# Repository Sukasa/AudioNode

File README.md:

# AudioNode
ESP8266/Teensy/VS1063a-based streaming audio node with MQTT integration

This project is the motherboard for a multi-mcu audio endpoint.  It uses three CPUs; a VS1063a does the heavy lifting for the audio decoding and is operated as a slave co-processor by the ESP8266.  A Teensy 3.2 also hangs off the ESP8266, being used as a sub-processor for the touch interface (7 capacitive touch points).  The ESP controls these two processors through a shared SPI bus, with the ESP as the bus master and the Teensy/VS1063a as SPI slaves.

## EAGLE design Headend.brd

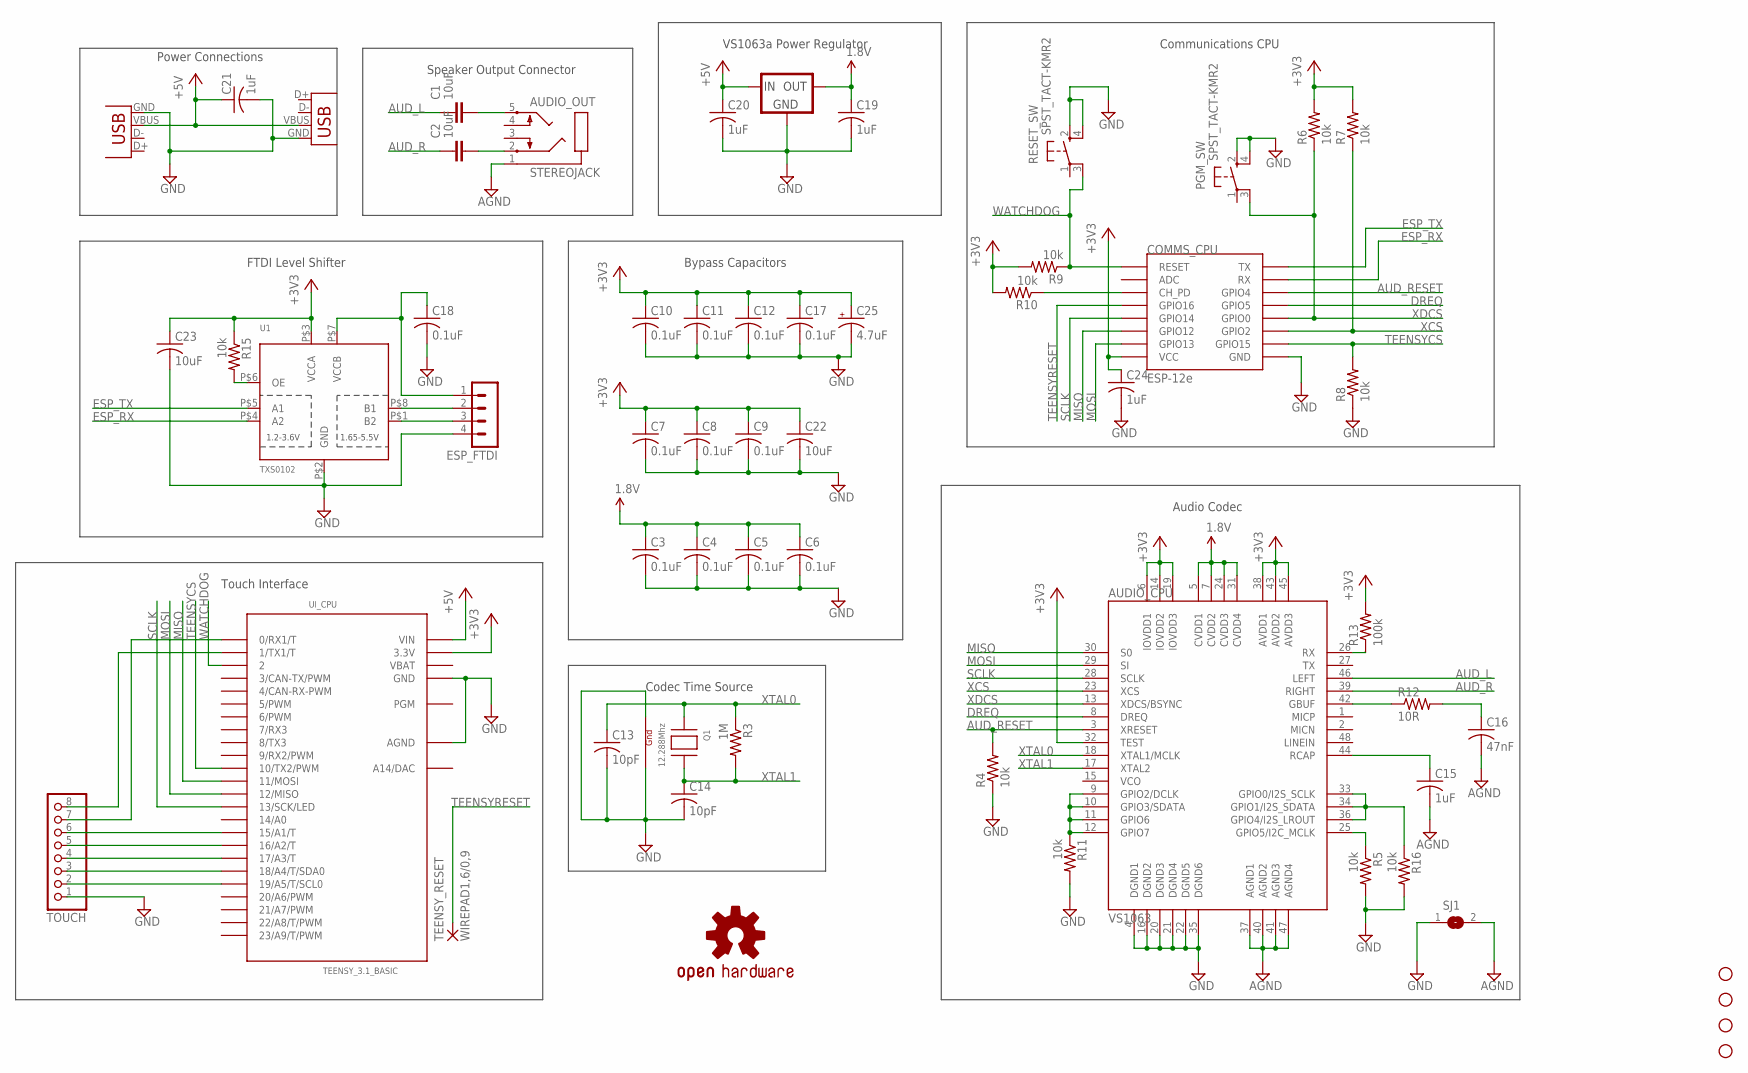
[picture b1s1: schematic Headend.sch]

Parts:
AUDIO_CPU: VS1063; LQFP-48
AUDIO_OUT: STEREOJACK; STX3100
C1, C2: 10uF; C805
C3, C4, C5, C6, C7, C8, C9, C10, C11, C12, C17, C18: 0.1uF; C0402
C13, C14: 10pF; C0402
C15, C24: 1uF; C0402
C16: 47nF; C0402
C19, C20, C21: 1uF; C0603
C22, C23: 10uF; C0402
C25: 4.7uF; PANASONIC_A
COMMS_CPU: ESP-12e; ESP12-SMD
ESP_FTDI: MA04-1
LOGO1: OSHW-LOGOL; OSHW-LOGO-L
PGM_SW: SPST_TACT-KMR2; KMR2
POWER_IN: USBSMD; USB-MINIB
Q1: 12.288Mhz; NX3225
R3: 1M; R0402
R4, R5, R6, R7, R8, R10, R11, R15, R16: 10k; R0402
R9: 10k; R0603
R12: 10R; R0402
R13: 100k; R0402
RESET_SW: SPST_TACT-KMR2; KMR2
SJ1: SJ
SPEAKER_PWR2: USB-A-S
STANDOFF1, STANDOFF2, STANDOFF3, STANDOFF4: STAND-OFF
TEENSY_RESET: WIREPAD1,6/0,9; 1,6/0,9
TOUCH: PINHD-1X8BIG; 1X08-BIG
U1: TXS0102; VFSOP-8
U2: AP7313; SOT23
UI_CPU: TEENSY_3.1_BASIC

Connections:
1.8V: AUDIO_CPU.5 (CVDD1), AUDIO_CPU.7 (CVDD2), AUDIO_CPU.24 (CVDD3), AUDIO_CPU.31 (CVDD4), C3.1, C4.1, C5.1, C6.1, C19.1, U2.2 (OUT)
+3V3: AUDIO_CPU.6 (IOVDD1), AUDIO_CPU.14 (IOVDD2), AUDIO_CPU.19 (IOVDD3), AUDIO_CPU.32 (TEST), AUDIO_CPU.38 (AVDD1), AUDIO_CPU.43 (AVDD2), AUDIO_CPU.45 (AVDD3), C7.1, C8.1, C9.1, C10.1, C11.1, C12.1, C17.1, C22.1, C23.1, C24.1, C25.+, COMMS_CPU.VCC, R6.2, R7.2, R9.2, R10.2, R13.2, R15.1, U1.P$3 (VCCA), UI_CPU.3.3V, UI_CPU.3.3V1 (3.3V)
+5V: C20.1, C21.1, POWER_IN.VBUS, SPEAKER_PWR2.VBUS, U2.1 (IN), UI_CPU.VIN
AGND: AUDIO_CPU.37 (AGND1), AUDIO_CPU.40 (AGND2), AUDIO_CPU.41 (AGND3), AUDIO_CPU.47 (AGND4), AUDIO_OUT.1, C15.2, C16.2, SJ1.2
AUD_L: AUDIO_CPU.46 (LEFT), C1.1
AUD_R: AUDIO_CPU.39 (RIGHT), C2.1
AUD_RESET: AUDIO_CPU.3 (XRESET), COMMS_CPU.GPIO4, R4.2
DREQ: AUDIO_CPU.8 (DREQ), COMMS_CPU.GPIO5
ESP_RX: COMMS_CPU.RXD0 (RX), U1.P$4 (A2)
ESP_TX: COMMS_CPU.TXD0 (TX), U1.P$5 (A1)
GND: AUDIO_CPU.4 (DGND1), AUDIO_CPU.16 (DGND2), AUDIO_CPU.20 (DGND3), AUDIO_CPU.21 (DGND4), AUDIO_CPU.22 (DGND5), AUDIO_CPU.35 (DGND6), C3.2, C4.2, C5.2, C6.2, C7.2, C8.2, C9.2, C10.2, C11.2, C12.2, C13.2, C14.2, C17.2, C18.2, C19.2, C20.2, C21.2, C22.2, C23.2, C24.2, C25.-, COMMS_CPU.GND, ESP_FTDI.4, PGM_SW.2 (S), PGM_SW.4 (S1), POWER_IN.GND, Q1.2 (G2), Q1.4 (G1), R4.1, R5.2, R8.1, R11.2, R16.2, RESET_SW.2 (S), RESET_SW.4 (S1), SJ1.1, SPEAKER_PWR2.GND, TOUCH.1, U1.P$2 (GND), U2.3 (GND), UI_CPU.AGND, UI_CPU.GND, UI_CPU.GND1 (GND)
MISO: AUDIO_CPU.30 (S0), COMMS_CPU.GPIO12, UI_CPU.11 (11/MOSI)
MOSI: AUDIO_CPU.29 (SI), COMMS_CPU.GPIO13, UI_CPU.12 (12/MISO)
unnamed: TOUCH.6, UI_CPU.15/A1 (15/A1/T)
unnamed: TOUCH.5, UI_CPU.16/A2 (16/A2/T)
unnamed: TOUCH.4, UI_CPU.17/A3 (17/A3/T)
unnamed: TOUCH.3, UI_CPU.18/A4 (18/A4/T/SDA0)
unnamed: TOUCH.2, UI_CPU.19/A5 (19/A5/T/SCL0)
unnamed: R15.2, U1.P$6 (OE)
unnamed: AUDIO_OUT.2, C2.2
unnamed: AUDIO_OUT.5, C1.2
unnamed: TOUCH.8, UI_CPU.1 (1/TX1/T)
unnamed: AUDIO_CPU.9 (GPIO2/DCLK), AUDIO_CPU.10 (GPIO3/SDATA), AUDIO_CPU.11 (GPIO6), AUDIO_CPU.12 (GPIO7), R11.1
unnamed: COMMS_CPU.CH_PD, R10.1
unnamed: AUDIO_CPU.33 (GPIO0/I2S_SCLK), AUDIO_CPU.34 (GPIO1/I2S_SDATA), AUDIO_CPU.36 (GPIO4/I2S_LROUT), R16.1
unnamed: AUDIO_CPU.44 (RCAP), C15.1
unnamed: AUDIO_CPU.42 (GBUF), R12.1
unnamed: C16.1, R12.2
unnamed: AUDIO_CPU.26 (RX), R13.1
unnamed: ESP_FTDI.2, U1.P$8 (B1)
unnamed: ESP_FTDI.3, U1.P$1 (B2)
unnamed: C18.1, ESP_FTDI.1, U1.P$7 (VCCB)
unnamed: TOUCH.7, UI_CPU.0 (0/RX1/T)
unnamed: AUDIO_CPU.25 (GPIO5/I2C_MCLK), R5.1
SCLK: AUDIO_CPU.28 (SCLK), COMMS_CPU.GPIO14, UI_CPU.13 (13/SCK/LED)
TEENSYCS: COMMS_CPU.GPIO15, R8.2, UI_CPU.10 (10/TX2/PWM)
TEENSYRESET: COMMS_CPU.GPIO16, TEENSY_RESET.1
VBAT: UI_CPU.VBAT
WATCHDOG: COMMS_CPU.RESET, R9.1, RESET_SW.3 (P1), UI_CPU.2
XCS: AUDIO_CPU.23 (XCS), COMMS_CPU.GPIO2, R7.1
XDCS: AUDIO_CPU.13 (XDCS/BSYNC), COMMS_CPU.GPIO0, PGM_SW.3 (P1), R6.1
XTAL0: AUDIO_CPU.18 (XTAL1/MCLK), C13.1, Q1.1 (X1), R3.1
XTAL1: AUDIO_CPU.17 (XTAL2), C14.1, Q1.3 (X2), R3.2

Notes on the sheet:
Power Connections
FTDI Level Shifter
Speaker Output Connector
VS1063a Power Regulator
Bypass Capacitors
Touch Interface
Codec Time Source
Communications CPU
Audio Codec

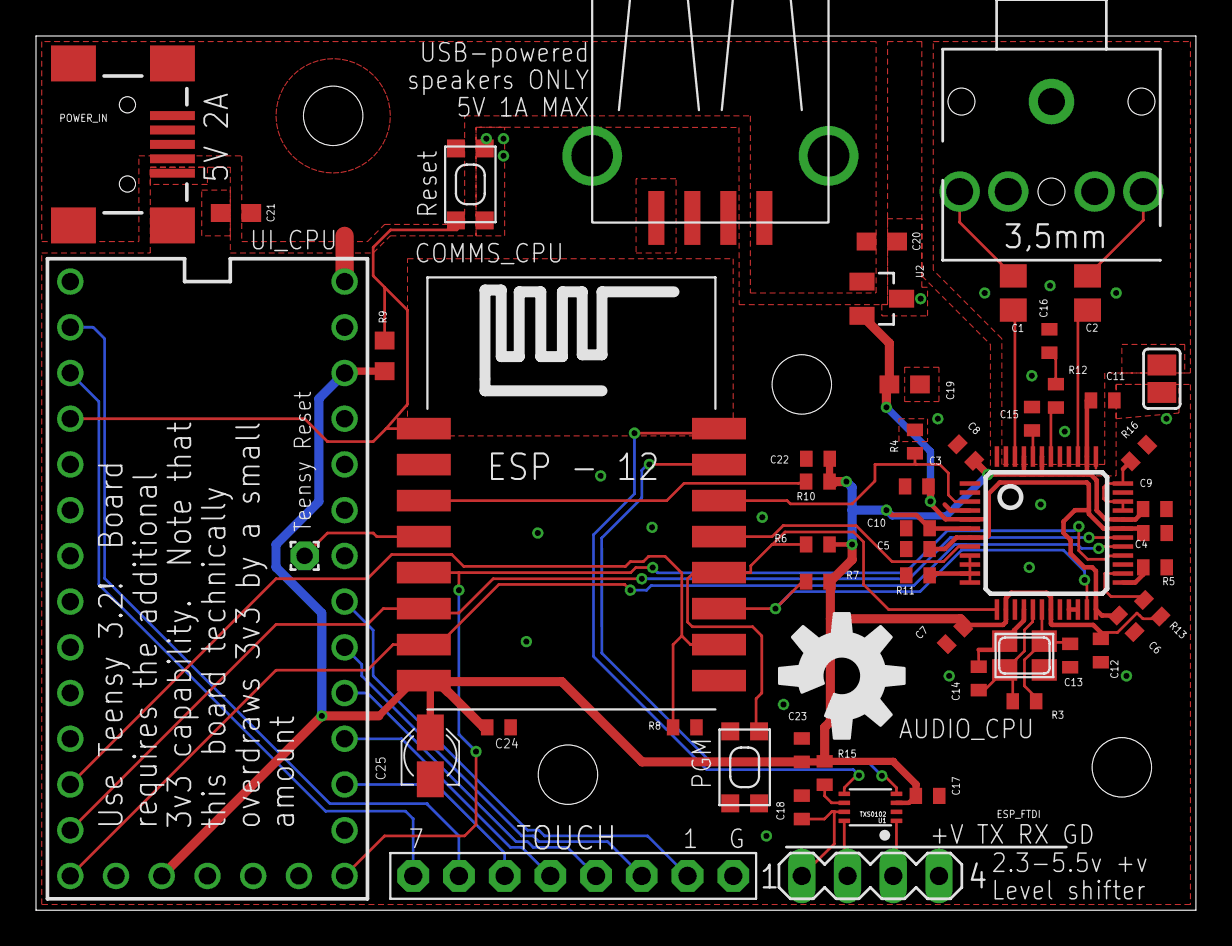
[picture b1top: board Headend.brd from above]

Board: 2 copper layers, 64.4 x 48.6 mm, 58 parts (0 on the bottom side), 42 nets.

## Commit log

2016-06-05 Add to Git
2016-06-05 Update board design
2016-06-06 Update board with further tweaks
2016-06-11 Update design, clean up spurious resistor between 3v3 and Gnd, clean up some routing
2016-06-17 Updated with more reddit feedback

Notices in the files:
parts and their libraries:
SparkFun-DigitalIC: Licensing: CC v3.0 Share-Alike You are welcome to use this library for commercial purposes.
